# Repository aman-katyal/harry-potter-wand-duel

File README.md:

# Harry Potter Wand Duel - RP2040 Embedded Edge-AI System

An interactive, dual-wand dueling system built on the Raspberry Pi RP2040 microcontroller. The wand tracks physical spell-casting gestures in real time using on-device machine learning (TinyML), transmits spell data wirelessly over 38 kHz modulated infrared, renders real-time combat status and animations on a 16x16 RGB LED matrix, and delivers tactile feedback via an onboard haptic motor driver.

Designed and developed for **ECE 362: Microprocessor Systems and Interfacing** at Purdue University.

---

## System Architecture

```
                      +-------------------------------------------------------+
                      |                 Raspberry Pi RP2040                   |
                      |                                                       |
                      |  +-------------------------------------------------+  |
                      |  | Core 0: Real-Time Engine & Peripherals          |  |
                      |  |                                                 |  |
                      |  |  * 74 Hz IMU Poller (BNO085 over I2C0)          |  |
                      |  |  * 3-Second 6-Axis Ring Buffer                  |  |
                      |  |  * WS2812 16x16 Matrix Controller (PIO + DMA)   |  |
                      |  |  * 38 kHz NEC IR Transmitter (PIO State Machine)|  |
                      |  |  * NEC Demodulating IR Receiver (PIO Interrupt) |  |
                      |  |  * DRV2605 Haptic Feedback (I2C0)               |  |
                      |  |  * Game State Machine, Health Bar & Shield Logic|  |
                      |  +-----------------------+-------------------------+  |
                      |                          |                             |
                      |                  Multicore Hardware                    |
                      |                    FIFO + Mutex                        |
                      |                          |                             |
                      |  +-----------------------v-------------------------+  |
                      |  | Core 1: TinyML Inference Engine                 |  |
                      |  |                                                 |  |
                      |  |  * Edge Impulse TFLite Micro Runtime            |  |
                      |  |  * 1650 ms Sliding Window Feature Extractor     |  |
                      |  |  * CMSIS-DSP Accelerated Neural Classifier      |  |
                      |  |  * K-Means Anomaly Detection Engine             |  |
                      |  +-------------------------------------------------+  |
                      +-------------------------------------------------------+
```

---

## Hardware Specifications

| Component | Part / IC | Interface | Description |
|---|---|---|---|
| **Microcontroller** | SparkFun Pro Micro RP2040 | Dual ARM Cortex-M0+ @ 133 MHz | Primary compute module with 264 KB SRAM and 2 MB Flash. |
| **Inertial Measurement** | Adafruit BNO085 | I2C0 (Fast Mode, 400 kHz) | 9-DOF IMU with onboard ARM Cortex-M0+ running Hillcrest SH-2 sensor fusion (Linear Accel + Rotation Vector). |
| **Haptics** | TI DRV2605L | I2C0 (Shared bus) | ERM/LRA haptic driver providing distinct wave sensations for spell casts, hits, and shield deployment. |
| **Display Matrix** | 16x16 WS2812B (256 LEDs) | PIO0 (Custom State Machine) | High-speed serialized 800 kHz pixel protocol driven directly by RP2040 PIO with no CPU bit-banging. |
| **IR Transmitter** | 940 nm High-Output IR LED | PIO1 (38 kHz Carrier Generator) | Hardware-timed NEC protocol encoding with 38 kHz carrier frequency modulation. |
| **IR Receiver** | TSOP38238 (38 kHz Demodulator) | PIO / Edge-triggered ISR | Demodulates incoming player commands and validates opponent player IDs. |
| **Shield Trigger** | Tactile Switch | GPIO 21 (Active High) | Hardware input to raise the defensive barrier and trigger hit immunity. |
| **Custom PCB** | 2-Layer KiCad Design | Multi-rail Power (5V / 3.3V) | Custom wand PCB integrating MCU, sensor breakouts, power regulation, and FET driver circuits. |

---

## Key Technical Challenges & Engineering Solutions

### 1. Dual-Core Real-Time Decoupling
Running TinyML neural network inference on continuous 6-axis sensor streams requires 60–90 ms of sustained computation per window. If executed synchronously on a single core:
- Sensor polling intervals would jitter, corrupting frequency-domain feature extraction.
- Incoming 38 kHz IR pulses would be dropped, causing missed hits during combat.
- LED matrix refresh routines would stall, resulting in visible visual stutter.

**Solution:** The system splits tasks across both RP2040 cores:
- **Core 0** handles strictly deterministic real-time tasks: reading the BNO085 at exactly 74 Hz, pushing samples to a circular buffer, rendering animations, managing IR transceiver state machines, and evaluating the duel state machine.
- **Core 1** operates as a co-processor dedicated solely to TinyML execution. When Core 0 detects an active gesture, it copies a 1650 ms sliding window (732 float features) into an exchange buffer and signals Core 1. Core 1 runs inference and returns a packed 32-bit result (`spell_id`, `confidence`, `anomaly_score`) via the RP2040 hardware FIFO.

### 2. False-Positive Filtering ("Leaky Bucket" Accumulator)
Natural wand handling and rapid arm movements can produce transient sensor spikes that momentarily fool an ML classifier.
- Instead of firing immediately on a single inference hit, the firmware uses an integrating leaky-bucket filter (`SPELL_TRIGGER_TARGET = 7`, `SPELL_DECAY_RATE = 2`).
- A spell is only cast when consecutive inferences consistently recognize the same gesture above the confidence threshold (`>= 0.90`).
- Individual spells use dynamic anomaly ceilings (e.g., `2.3` for Aguamenti vs. `2.6` for Stupefy) to cleanly reject out-of-distribution movements.

### 3. Hardware Peripheral Offloading via PIO
- **WS2812B Protocol:** Rather than tying up the CPU with tight assembly loops for the strict 800 kHz NZR timing, a custom PIO program streams pixel color buffers directly to the matrix.
- **38 kHz IR Modulation:** The 38 kHz carrier square wave and NEC pulse-distance bit-timing are generated in hardware using a PIO state machine, ensuring precise modulation independent of CPU load.

---

## Combat & Game Mechanics

- **Spells:**
  - **Aguamenti (Water Spell):** Forward-sweeping motion -> triggers blue matrix firework animation, distinct haptic vibration, and broadcasts NEC command `10` over IR. Deals 2 damage.
  - **Stupefy (Stun Spell):** Sharp diagonal slash -> triggers red matrix firework animation, heavy haptic jolt, and broadcasts NEC command `20` over IR. Deals 2 damage.
- **Protego (Shield):** Pressing the shield button deploys an animated protective blue barrier on the matrix for 1.5 seconds. During this window, any incoming IR hits are flushed from the queue and ignored (temporary immunity). A 10-second cooldown timer is enforced before the shield can be redeployed.
- **Health System:** A perimeter health bar tracks player health (initialized to 10 HP). When health drops to 0, an animated defeat screen is displayed and casting is locked out until respawn.
- **Multiplayer Duel Configuration:**
  - In [`firmware/src/sys_config.h`](firmware/src/sys_config.h), set `PLAYER_ID` to `1` or `2` to assign wand identity.
  - Set `ALLOW_SELF_HIT` to `1` for single-wand solo testing, or `0` for two-player competitive duels (to prevent bouncing off walls and self-inflicting damage).

---

## Hardware Pinout Map

| RP2040 GPIO | Function | Peripheral |
|---|---|---|
| **GPIO 4** | I2C0 SDA | BNO085 IMU & DRV2605 Haptic Driver |
| **GPIO 5** | I2C0 SCL | BNO085 IMU & DRV2605 Haptic Driver |
| **GPIO 6** | Input / PIO | TSOP38238 38 kHz IR Receiver |
| **GPIO 16** | Output / PIO | IR LED Driver (38 kHz modulated output) |
| **GPIO 20** | Output / PIO | WS2812B 16x16 LED Matrix Data Line |
| **GPIO 21** | Input (Pull-Down) | Shield Tactile Switch |

---

## Repository Structure

```
.
├── firmware/                   # Primary dual-core wand firmware (PlatformIO project)
│   ├── src/                    # Application source files
│   │   ├── main.c              # Core 0 loop, hardware init, duel logic, IR/LED handling
│   │   ├── sys_config.h        # Pin assignments, tuning thresholds, player identity
│   │   ├── ei_bridge.cpp       # Edge Impulse C++ wrapper for Core 1 inference
│   │   └── ei_bridge.h
│   ├── lib/                    # Device drivers and neural network model
│   │   ├── Adafruit_BNO08x/    # Hillcrest SH-2 IMU driver
│   │   ├── haptics/            # DRV2605 haptic motor driver
│   │   ├── ir_receiver/        # NEC IR decoder implementation
│   │   ├── ir_transmitter/     # NEC IR encoder & emitter
│   │   ├── led_matrix/         # Matrix animations (fireworks, shield, healthbar)
│   │   └── edge-impulse-model/ # Exported TinyML model with CMSIS-DSP kernels
│   ├── pio/                    # PIO assembly files (WS2812 timing, IR carrier)
│   └── platformio.ini          # Build configuration (Pico-SDK, multicore, CMSIS flags)
│
├── hardware/                   # KiCad electrical design & PCB layout
│   ├── ece362project.kicad_sch # Top-level schematic
│   ├── ece362project.kicad_pcb # 2-layer routed PCB layout
│   ├── *.kicad_sch             # Hierarchical schematic sheets (power, IMU, haptics, etc.)
│   ├── components/             # Custom footprints and symbol libraries
│   └── manufacturing/          # Fabrication gerber files, drill files, and BOM
│
├── prototypes/                 # Isolated subsystem test benches used during bring-up
│   ├── haptics/                # DRV2605 waveform testing
│   ├── imu/                    # BNO08x orientation & acceleration logging
│   ├── ir_receiver/            # IR receiver timing & decoding tests
│   ├── ir_transmitter/         # IR transmitter carrier & burst verification
│   └── led_matrix/             # LED animation test bench
│
└── archive/                    # Developmental prototype snapshots
```

---

## Building & Flashing

### Prerequisites
- [PlatformIO Core](https://platformio.org/) (CLI) or PlatformIO IDE extension for VS Code.
- Raspberry Pi Pico toolchain with Pico-SDK support.
- A SWD debugger (e.g. Raspberry Pi Picoprobe) or standard USB BOOTSEL drag-and-drop.

### Build
Navigate to the firmware directory and compile:
```bash
cd firmware
pio run
```

### Flash via Picoprobe
```bash
pio run -t upload
```

### Serial Monitor
To view real-time debug telemetry (gesture scores, anomaly ratings, hit events):
```bash
pio device monitor -b 115200
```

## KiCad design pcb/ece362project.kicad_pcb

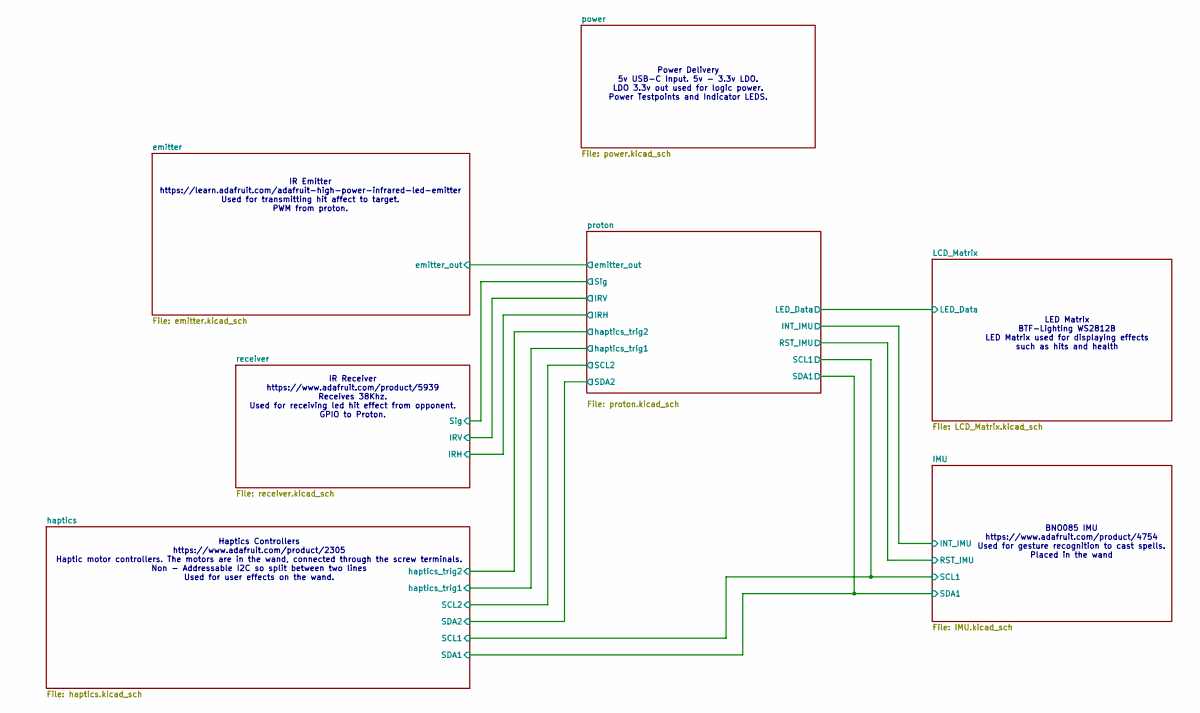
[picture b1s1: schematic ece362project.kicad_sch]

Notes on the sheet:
IR Emitter https://learn.adafruit.com/adafruit-high-power-infrared-led-emitter Used for transmitting hit affect to target. PWM from proton.
LED Matrix BTF-Lighting WS2812B LED Matrix used for displaying effects such as hits and health
BNO085 IMU https://www.adafruit.com/product/4754 Used for gesture recognition to cast spells. Placed in the wand
Power Delivery 5v USB-C Input. 5v - 3.3v LDO. LDO 3.3v out used for logic power. Power Testpoints and Indicator LEDS.
Haptics Controllers https://www.adafruit.com/product/2305 Haptic motor controllers. The motors are in the wand, connected through the screw terminals. Non - Addressable I2C so split between two lines Used for user effects on the wand.
IR Receiver https://www.adafruit.com/product/5939 Receives 38Khz. Used for receiving led hit effect from opponent. GPIO to Proton.

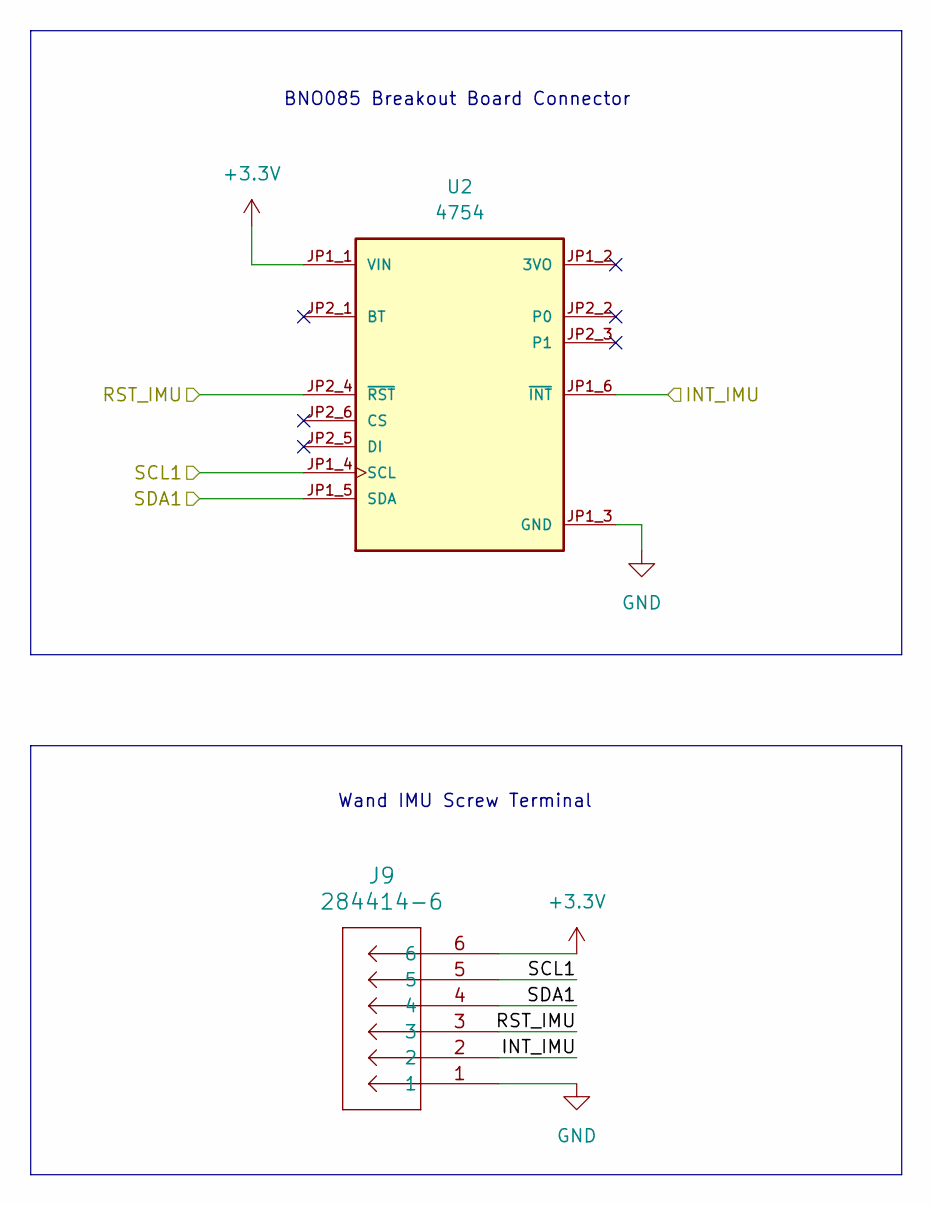
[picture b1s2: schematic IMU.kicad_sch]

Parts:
J9: 284414-6; CONN6_284414-6_TEC
U2: 4754; MODULE_4754; PARTREV 2021-03-16

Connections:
/IMU/INT_IMU: J9.3, U2.JP1_6 (~INT); also elsewhere on the board
/IMU/RST_IMU: J9.2, U2.JP2_4 (~RST); also elsewhere on the board
GND: J9.1, U2.JP1_3 (GND); also elsewhere on the board

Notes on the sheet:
BNO085 Breakout Board Connector
Wand IMU Screw Terminal

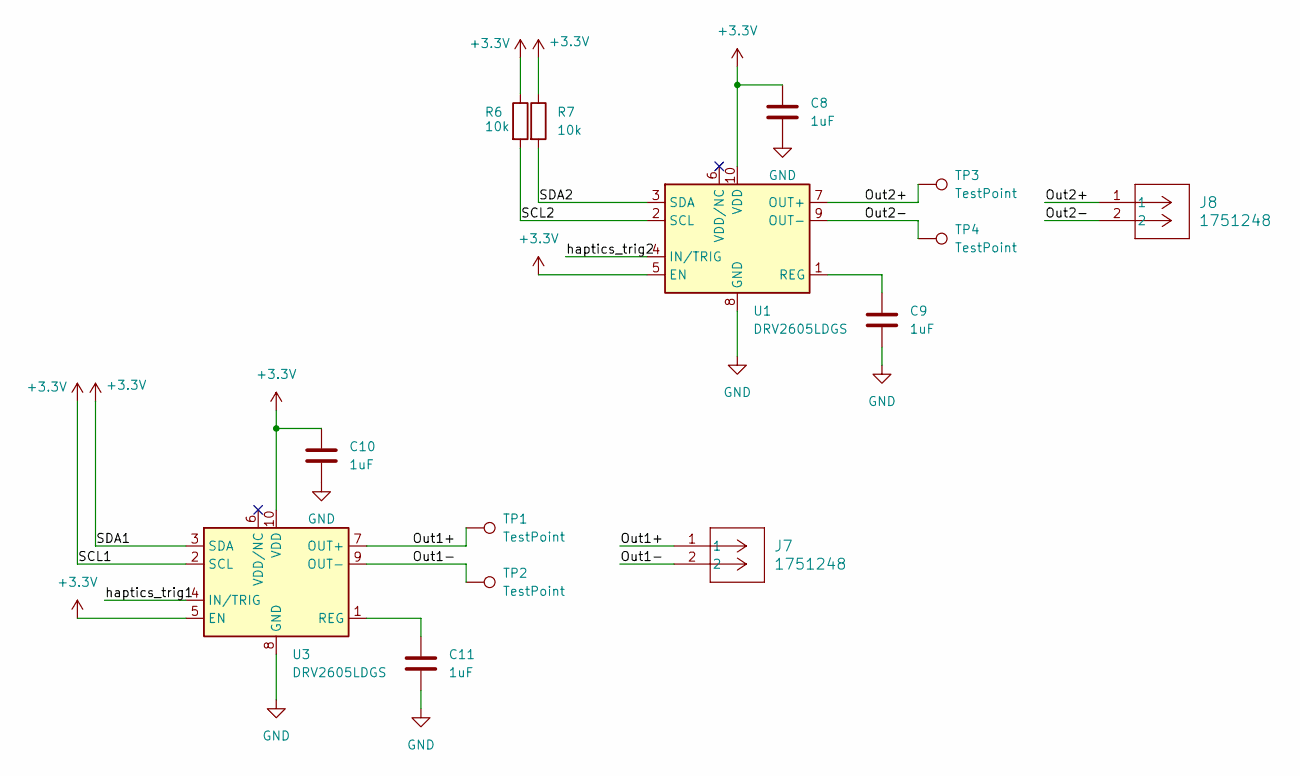
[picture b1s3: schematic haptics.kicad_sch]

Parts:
C8, C9, C10, C11: 1uF
J7, J8: 1751248; CONN_1751248_PXC
R6, R7: 10k
TP1, TP2, TP3, TP4: TestPoint; TestPoint_Pad_3.0x3.0mm
U1, U3: DRV2605LDGS; VSSOP-10_3x3mm_P0.5mm

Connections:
/haptics/Out1+: J7.1, TP1.1, U3.7 (OUT+)
/haptics/Out1-: J7.2, TP2.1, U3.9 (OUT-)
/haptics/Out2+: J8.1, TP3.1, U1.7 (OUT+)
/haptics/Out2-: J8.2, TP4.1, U1.9 (OUT-)
/haptics/SCL2: R6.2, U1.2 (SCL); also elsewhere on the board
/haptics/SDA2: R7.2, U1.3 (SDA); also elsewhere on the board
/haptics/haptics_trig1: U3.4 (IN/TRIG); also elsewhere on the board
/haptics/haptics_trig2: U1.4 (IN/TRIG); also elsewhere on the board
GND: C8.2, C9.2, C10.2, C11.2, U1.8 (GND), U3.8 (GND); also elsewhere on the board
unnamed: C9.1, U1.1 (REG)
unnamed: C11.1, U3.1 (REG)

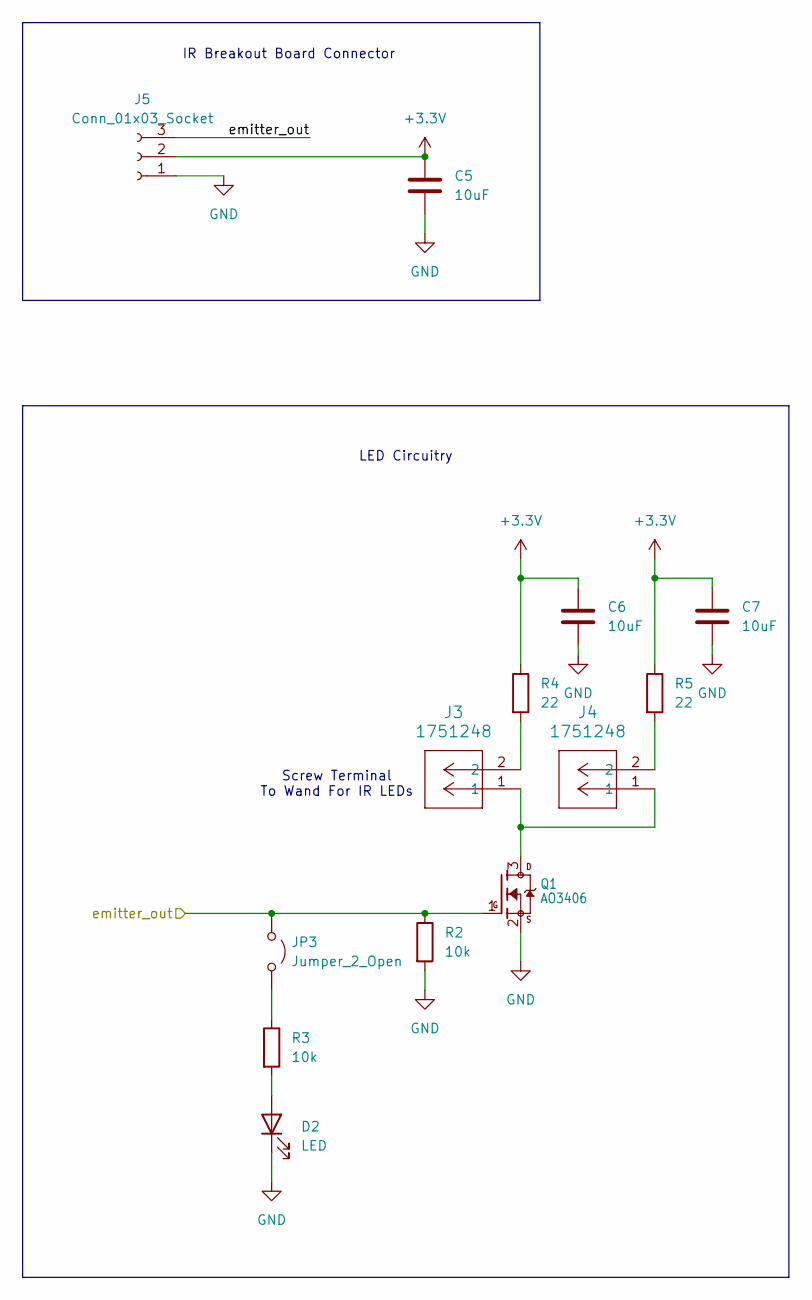
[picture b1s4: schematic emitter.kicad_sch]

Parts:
C5, C6, C7: 10uF; C_0603_1608Metric
D2: LED; LED_0603_1608Metric
J3, J4: 1751248; CONN_1751248_PXC
J5: Conn_01x03_Socket; PinSocket_1x03_P2.54mm_Vertical
JP3: Jumper_2_Open; TestPoint_2Pads_Pitch2.54mm_Drill0.8mm
Q1: AO3406; SOT23-WIDE
R2, R3: 10k; R_0603_1608Metric
R4, R5: 22; R_0603_1608Metric

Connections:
/emitter/emitter_out: J5.3, JP3.1 (A), Q1.1 (G), R2.1; also elsewhere on the board
GND: C5.2, C6.2, C7.2, D2.1 (K), J5.1, Q1.2 (S), R2.2; also elsewhere on the board
unnamed: D2.2 (A), R3.2
unnamed: J3.2, R4.2
unnamed: J4.2, R5.2
unnamed: JP3.2 (B), R3.1
unnamed: J3.1, J4.1, Q1.3 (D)

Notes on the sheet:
Screw Terminal To Wand For IR LEDs
IR Breakout Board Connector
LED Circuitry

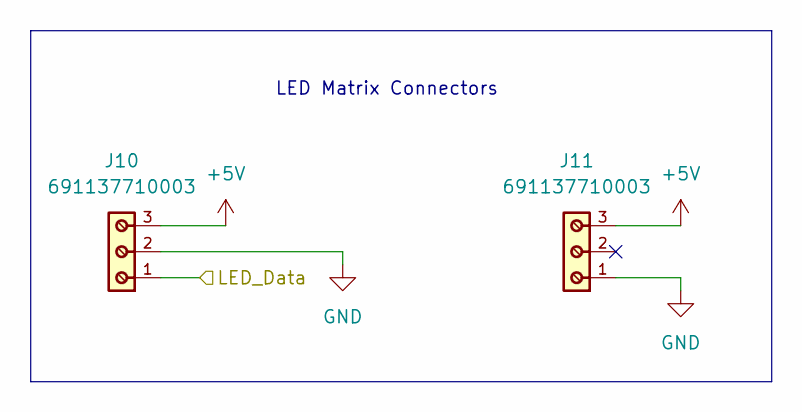
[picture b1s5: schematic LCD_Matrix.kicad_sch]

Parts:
J10, J11: 691137710003

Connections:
+5V: J10.3, J11.3; also elsewhere on the board
/LCD_Matrix/LED_Data: J10.1; also elsewhere on the board
GND: J10.2, J11.1; also elsewhere on the board

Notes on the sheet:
LED Matrix Connectors

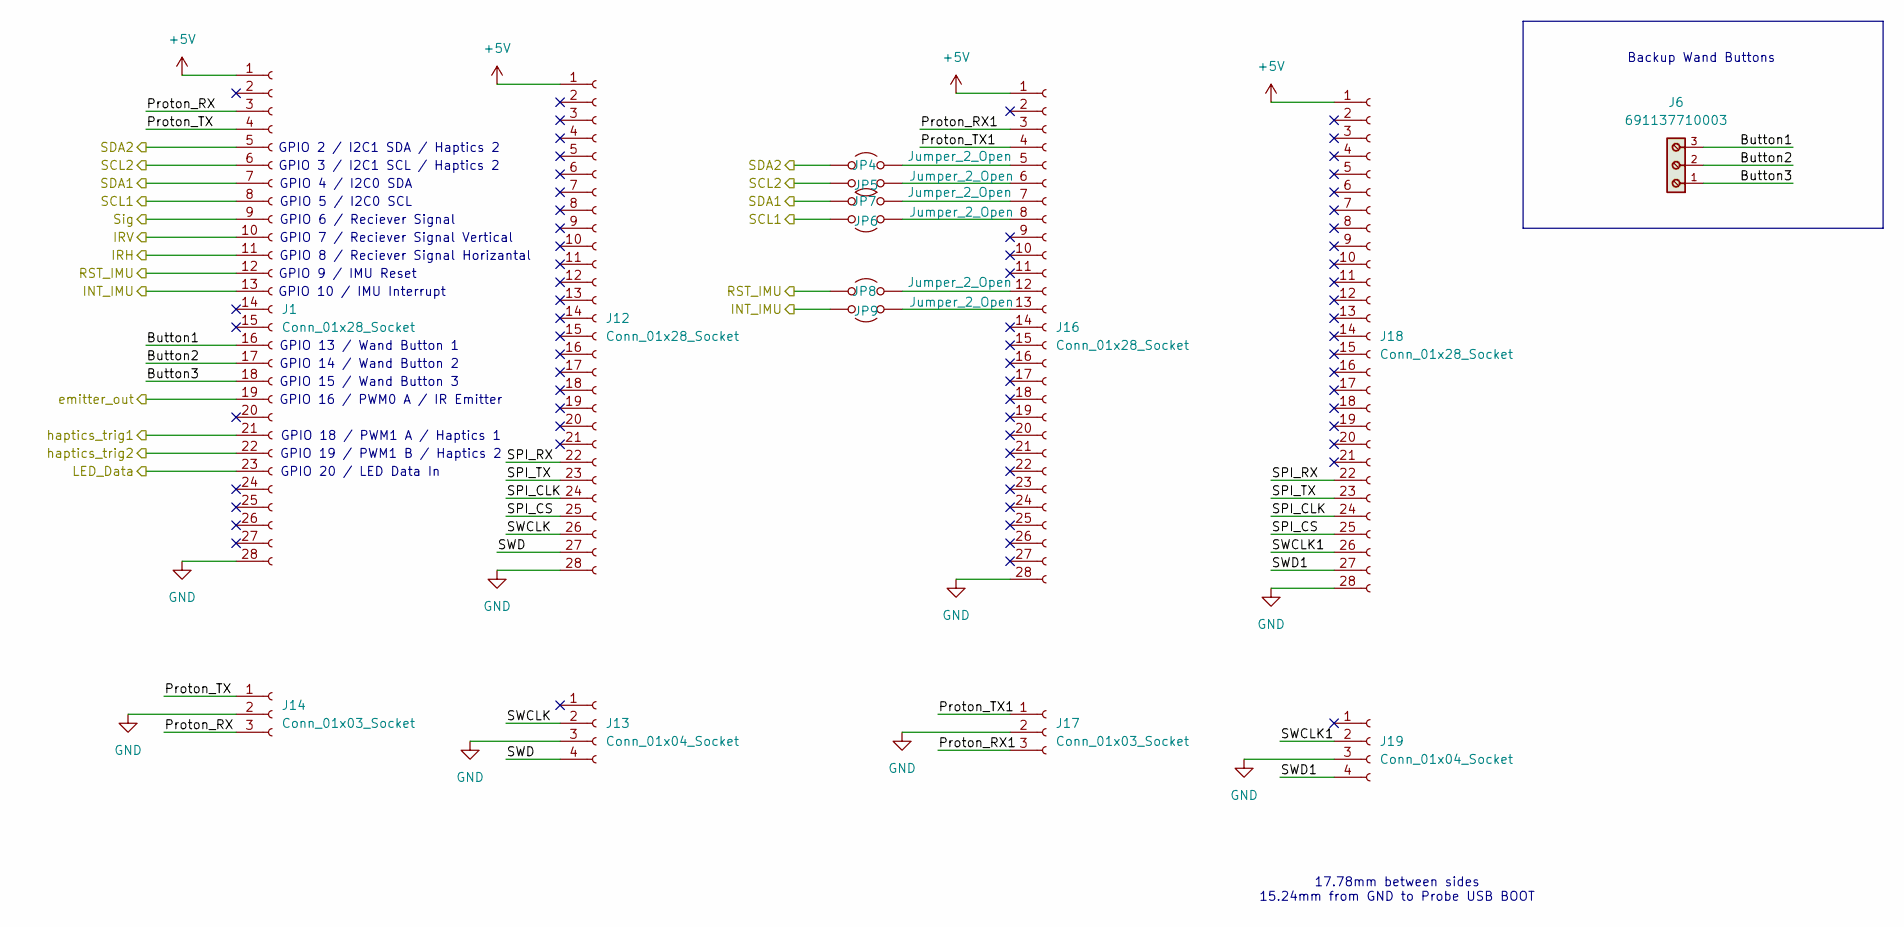
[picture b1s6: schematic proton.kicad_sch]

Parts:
J1, J12, J16, J18: Conn_01x28_Socket; PinSocket_1x28_P2.54mm_Vertical
J6: 691137710003
J13, J19: Conn_01x04_Socket; PinHeader_1x04_P2.54mm_Vertical
J14, J17: Conn_01x03_Socket; PinSocket_1x03_P2.54mm_Vertical
JP4, JP5, JP6, JP7, JP8, JP9: Jumper_2_Open; TestPoint_2Pads_Pitch2.54mm_Drill0.8mm

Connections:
+5V: J1.1, J12.1, J16.1, J18.1; also elsewhere on the board
/IMU/INT_IMU: J1.13, JP9.2 (B); also elsewhere on the board
/IMU/RST_IMU: J1.12, JP8.1 (A); also elsewhere on the board
/LCD_Matrix/LED_Data: J1.23; also elsewhere on the board
/emitter/emitter_out: J1.19; also elsewhere on the board
/haptics/SCL2: J1.6, JP5.2 (B); also elsewhere on the board
/haptics/SDA2: J1.5, JP4.1 (A); also elsewhere on the board
/haptics/haptics_trig1: J1.21; also elsewhere on the board
/haptics/haptics_trig2: J1.22; also elsewhere on the board
/proton/Button1: J1.16, J6.3
/proton/Button2: J1.17, J6.2
/proton/Button3: J1.18, J6.1
/proton/IRH: J1.11; also elsewhere on the board
/proton/IRV: J1.10; also elsewhere on the board
/proton/Proton_RX: J1.3, J14.3
/proton/Proton_RX1: J16.3, J17.3
/proton/Proton_TX: J1.4, J14.1
/proton/Proton_TX1: J16.4, J17.1
/proton/SPI_CLK: J12.24, J18.24
/proton/SPI_CS: J12.25, J18.25
/proton/SPI_RX: J12.22, J18.22
/proton/SPI_TX: J12.23, J18.23
/proton/SWCLK: J12.26, J13.2
/proton/SWCLK1: J18.26, J19.2
/proton/SWD: J12.27, J13.4
/proton/SWD1: J18.27, J19.4
/proton/Sig: J1.9; also elsewhere on the board
GND: J1.28, J12.28, J13.3, J14.2, J16.28, J17.2, J18.28, J19.3; also elsewhere on the board
unnamed: J16.5, JP4.2 (B)
unnamed: J16.6, JP5.1 (A)
unnamed: J16.7, JP7.2 (B)
unnamed: J16.8, JP6.1 (A)
unnamed: J16.12, JP8.2 (B)
unnamed: J16.13, JP9.1 (A)

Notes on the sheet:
GPIO 7 / Reciever Signal Vertical
GPIO 15 / Wand Button 3
Backup Wand Buttons
GPIO 16 / PWM0 A / IR Emitter
GPIO 6 / Reciever Signal
GPIO 2 / I2C1 SDA / Haptics 2
GPIO 8 / Reciever Signal Horizantal
GPIO 5 / I2C0 SCL
GPIO 18 / PWM1 A / Haptics 1
GPIO 20 / LED Data In
GPIO 14 / Wand Button 2
GPIO 13 / Wand Button 1
GPIO 4 / I2C0 SDA
GPIO 9 / IMU Reset
GPIO 19 / PWM1 B / Haptics 2
17.78mm between sides 15.24mm from GND to Probe USB BOOT
GPIO 3 / I2C1 SCL / Haptics 2
GPIO 10 / IMU Interrupt

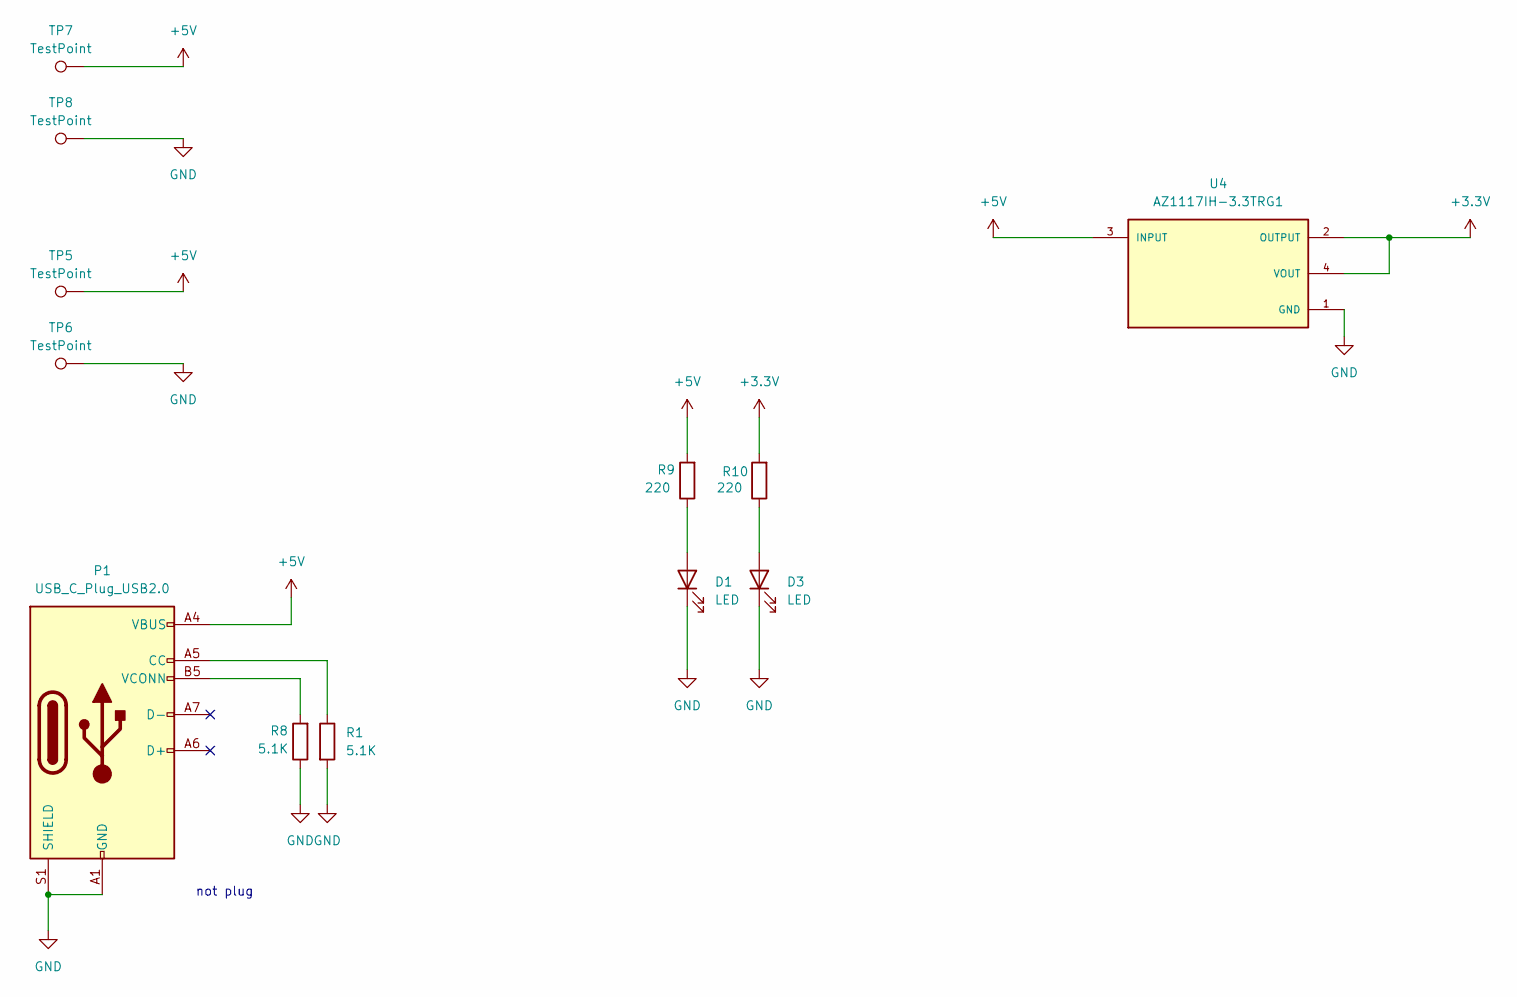
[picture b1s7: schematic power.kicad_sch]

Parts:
D1, D3: LED
P1: USB_C_Plug_USB2.0
R1, R8: 5.1K
R9, R10: 220
TP5, TP6, TP7, TP8: TestPoint
U4: AZ1117IH-3.3TRG1; SOT230P700X185-4N; PARTREV 2-2

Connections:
+5V: P1.A4 (VBUS), P1.A9 (VBUS), P1.B4 (VBUS), P1.B9 (VBUS), R9.2, TP5.1, TP7.1, U4.3 (INPUT); also elsewhere on the board
GND: D1.1 (K), D3.1 (K), P1.A1 (GND), P1.A12 (GND), P1.B1 (GND), P1.B12 (GND), P1.S1 (SHIELD), R1.2, R8.1, TP6.1, TP8.1, U4.1 (GND); also elsewhere on the board
unnamed: D1.2 (A), R9.1
unnamed: D3.2 (A), R10.1
unnamed 37: P1.A5 (CC), R1.1; also elsewhere on the board
unnamed 38: P1.B5 (VCONN), R8.2; also elsewhere on the board

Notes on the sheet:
not plug

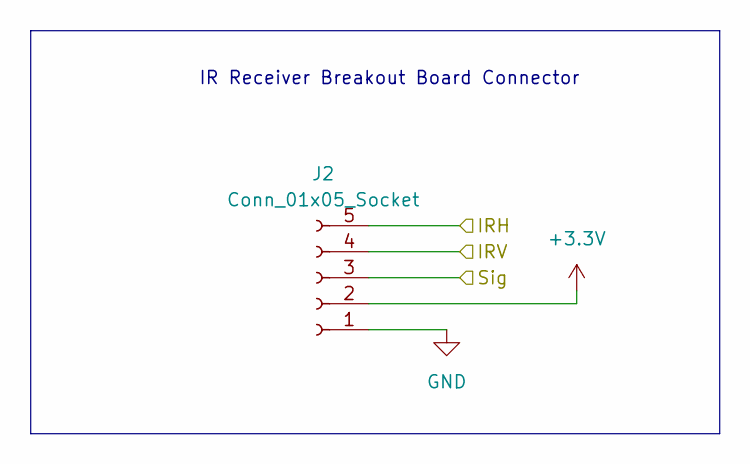
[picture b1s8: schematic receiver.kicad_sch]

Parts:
J2: Conn_01x05_Socket; PinHeader_1x05_P2.54mm_Vertical

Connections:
/proton/IRH: J2.5; also elsewhere on the board
/proton/IRV: J2.4; also elsewhere on the board
/proton/Sig: J2.3; also elsewhere on the board
GND: J2.1; also elsewhere on the board

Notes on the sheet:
IR Receiver Breakout Board Connector

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
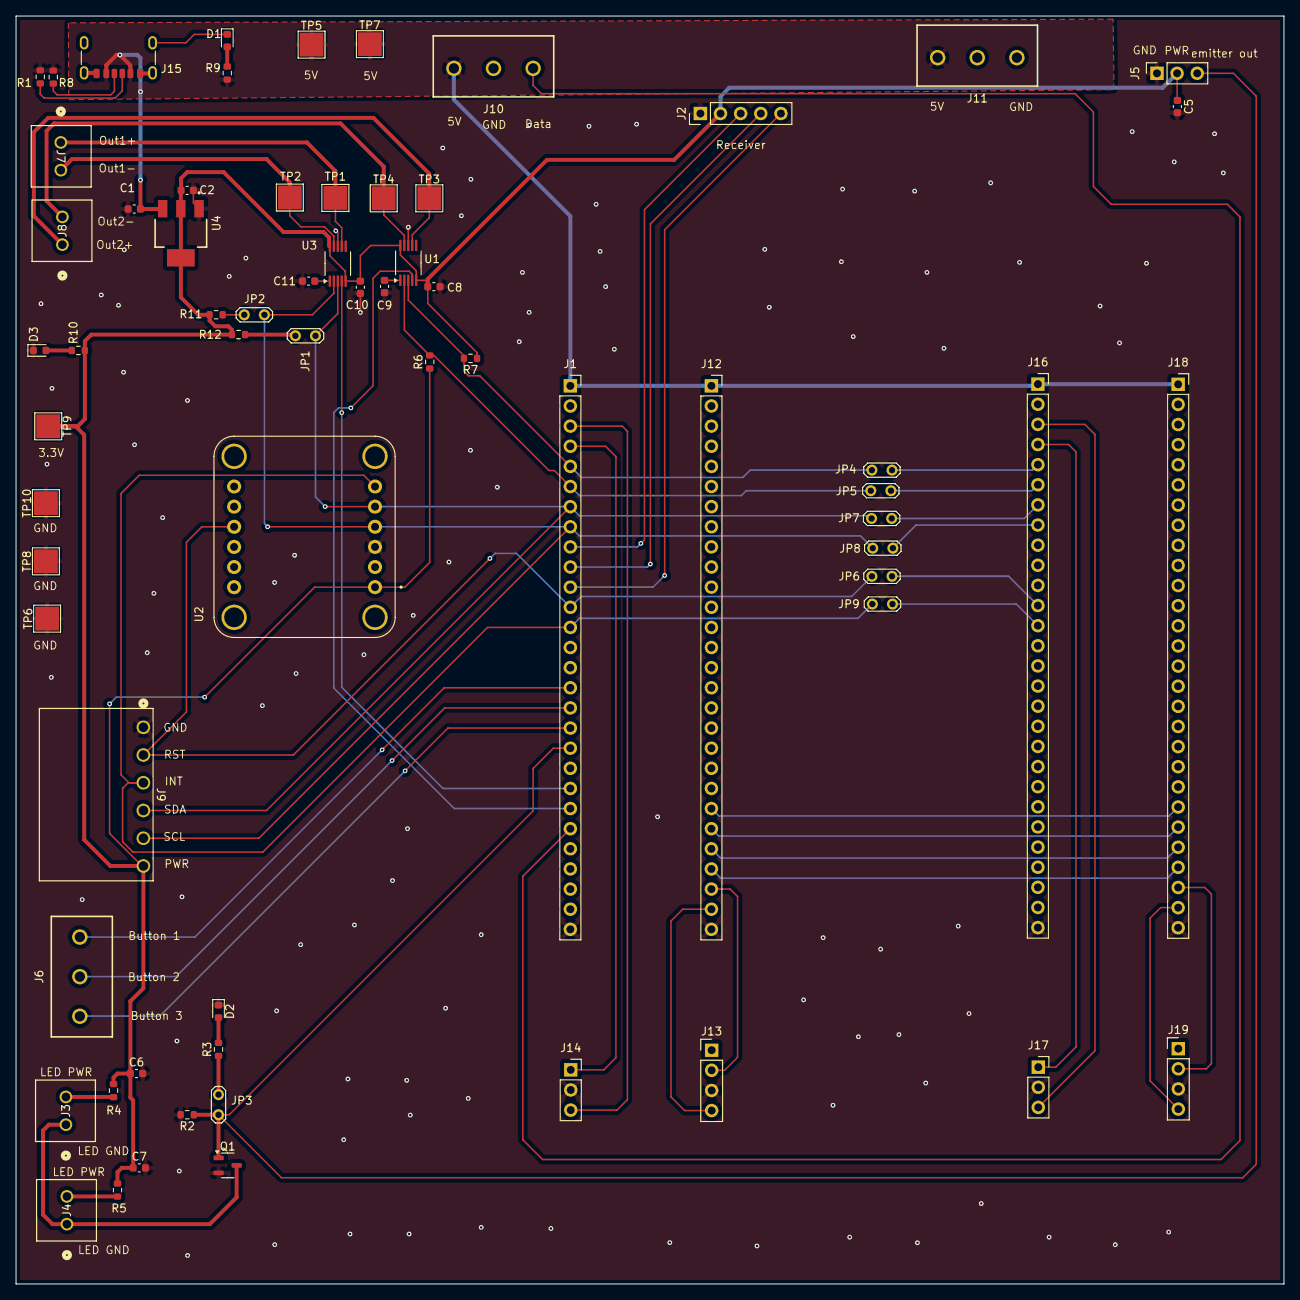
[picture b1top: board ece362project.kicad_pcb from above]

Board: 2 copper layers, 160.0 x 160.0 mm, 67 parts (0 on the bottom side), 54 nets.

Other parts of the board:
C1: 10uF; C_0603_1608Metric
C2: 22uF; C_0603_1608Metric
J15: USB_C_Receptacle_PowerOnly_6P; USB_C_Receptacle_GCT_USB4125-xx-x-0190_6P_TopMnt_Horizontal
JP1, JP2: Jumper_2_Open; TestPoint_2Pads_Pitch2.54mm_Drill0.8mm
R11, R12: 10k; R_0603_1608Metric
TP9, TP10: TestPoint; TestPoint_Pad_3.0x3.0mm

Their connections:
+5V: C1.1, J15.A9 (VBUS), J15.B9 (VBUS); also elsewhere on the board
GND: C1.2, C2.2, J15.A12 (GND), J15.B12 (GND), J15.S1 (SHIELD), TP10.1; also elsewhere on the board
unnamed 37: J15.A5 (CC1); also elsewhere on the board
unnamed 38: J15.B5 (CC2); also elsewhere on the board
unnamed: JP1.1 (A), R12.2
unnamed: JP2.1 (A), R11.2

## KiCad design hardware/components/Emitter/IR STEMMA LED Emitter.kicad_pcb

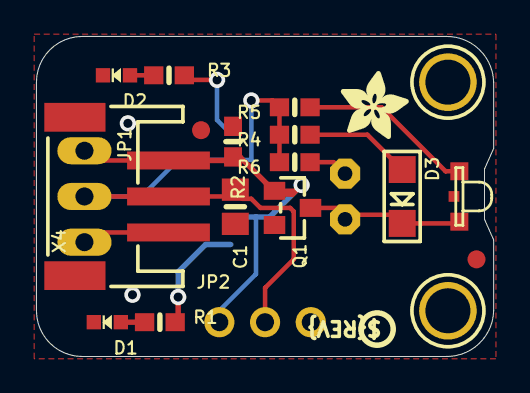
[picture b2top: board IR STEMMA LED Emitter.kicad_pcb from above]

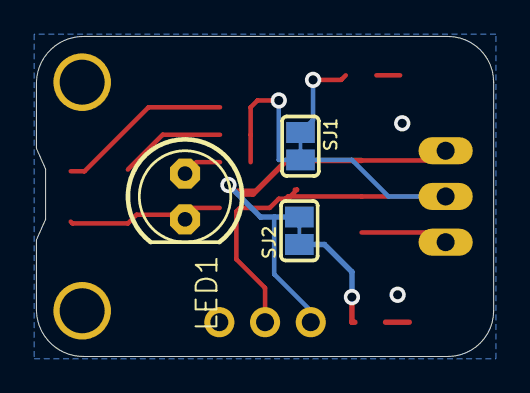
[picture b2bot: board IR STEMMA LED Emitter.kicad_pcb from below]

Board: 16 copper layers, 25.4 x 17.8 mm, 39 parts (14 on the bottom side), 11 nets.

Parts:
C1: 10uF; 0805-NO
D1: RED; CHIPLED_0603_NOOUTLINE
D2: GREEN; CHIPLED_0603_NOOUTLINE
D3: 1206 IR 940nm; CHIPLED_1206
D4: 1206 IR 940nm Side; LED_1206_SIDE
FID2, FID3: FIDUCIAL_1MM
JP1: 0.1" Header; 1X03_OVAL
JP2: 0.1" Header; 1X03_ROUND
LED1: 5mm; LED5MM
PLABEL0: PLABEL0
PLABEL00: PLABEL00
PLABEL1: PLABEL1
PLABEL2: PLABEL2
PLABEL3: PLABEL3
PLABEL4: PLABEL4
PLABEL5: PLABEL5
PLABEL6: PLABEL6
PLABEL7: PLABEL7
PLABEL8: PLABEL8
PLABEL9: PLABEL9
PLABEL10: PLABEL10
PLABEL11: PLABEL11
PLABEL13: PLABEL13
PLABEL14: PLABEL14
Q1: AO3406; SOT23-WIDE
R1, R2: 10K; 0603-NO
R3: 33K; 0603-NO
R4, R5, R6: 22; 0603-NO
SJ1, SJ2: SOLDERJUMPER_CLOSEDWIRE
U$1, U$8: MOUNTINGHOLE2.5; MOUNTINGHOLE_2.5_PLATED
U$5: PCBFEAT-REV-040
U$10: ADAFRUIT_3.5MM
X4: JST PH 3; JSTPH3

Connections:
GND: C1.2, D1.C, D2.C, JP1.3, JP2.3, Q1.2, R2.1, X4.1
unnamed: R3.2, SJ1.1
unnamed: D1.A, R1.1
unnamed: R1.2, SJ2.1
unnamed: D3.C, D4.C, LED1.K, Q1.3
unnamed: D3.A, R4.1
unnamed: D4.A, R5.1
unnamed: LED1.A, R6.1
unnamed: D2.A, R3.1
SIGNAL: JP1.1, JP2.1, Q1.1, R2.2, SJ2.2, X4.3
VIN: C1.1, JP1.2, JP2.2, R4.2, R5.2, R6.2, SJ1.2, X4.2

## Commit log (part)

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2025-10-26 initial
2025-10-26 initial IR code
2025-10-26 added files to imu
2025-10-26 restart vscode
2025-10-31 added new files for imu
2025-10-31 somewhat works (IMU)
2025-11-02 kinda working IR Receiver and changed project structure folders
2025-11-02 rrrrrr
2025-11-02 simpler protocol?
2025-11-06 stuff
2025-11-06 finished imu code basically
2025-11-06 done some animations
2025-11-07 updated animation
2025-11-07 emitter transmit code
2025-11-07 receiver works fully now
2025-11-09 made it more efficient
2025-11-10 refactored code
2025-11-11 combined emit/rec into IR library
    1. moved ir_receiver_lib from IR_Receiver folder into IR
    2. moved ir_emitter.c and ir_emitter.h from IR_Transmitter into IR
    3. created a new main.c for IR that should constantly be checking for received data while also able to set a T/F flag to send data from one player to another
2025-11-11 copied moved files back into original folders
    Added back the files moved into IR folder (receiver lib, .c/.h files for emitter) back into their respective IR_Receiver and IR_Transmitter folders just in case we want to test separately in the futu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
2025-11-11 will stop looping after transmit
2025-11-11 fixed a dependency issue
2025-11-11 using non-blocking dma
2025-11-11 added ini file to IR folder
2025-11-11 moved ini file
2025-11-11 fixed dependency
2025-11-11 Clean up main.c by removing comments and sleep
    Removed unnecessary comments and sleep function to streamline the main application loop.
2025-11-11 "colors working for LED"
2025-11-11 deleted unnecessary prints/comments
2025-11-11 made haptics code a bit more efficient
2025-11-11 added haptic feedback when emitting
2025-11-11 "added another animation"
2025-11-13 worked on dma
2025-11-14 added animations
2025-11-14 minimal
2025-11-14 integraed LED
2025-11-14 changed test spell
2025-11-14 model and data
2025-11-16 LED Matrix works without color
2025-11-16 commit before big restructure, everything mostly works well
2025-11-16 led matrix done
2025-11-16 integration setup
2025-11-17 button integration
2025-11-17 button works
2025-11-19 new model and model testing code
2025-11-20 working
2025-11-20 led matrix
2025-11-20 getdetection function
2025-11-20 multicore
2025-11-20 done
2025-11-21 board
2025-11-21 most recent code with the dual core
    works
2025-12-03 pushing for fun
2025-12-03 commented haptics
2025-12-03 added comments
2025-12-03 edidted files cleaner concise comments
2025-12-12 edited all the animations run rightside up
2025-12-12 maybe working
2025-12-12 player id
2025-12-12 fixed
